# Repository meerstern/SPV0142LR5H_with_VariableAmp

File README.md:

# 可変アンプ内蔵アナログ出力MEMSマイク変換基板 SPV0142LR5H
The Converter board of SPV0142LR5H with Variable Apmlifer

## 概要

  * 最大約50倍の増幅回路[TLV316][0]Syntiant社製[アナログ出力MEMSマイクSPV0142LR5H][1]を搭載した2.54mmピッチ変換基板です。  
  * 可聴音から超音波(100Hz～80kHz)までの幅広い帯域を高感度にセンシングすることが可能です。  
  * 周波数特性が非常にフラットです(20Hz-10kHz±2dB、10kHz-80kHz±10dB)
  * 超音波センサや超音波通信などに使用可能です。  
  * RV1により約1倍～約50倍まで変更することが可能です。  
  * アンプ回路を搭載することでArduinoといったマイコンのアナログ入力に直接接続できます。  
  * マイク穴は基板裏面の丸印部分です。  
  * 電源電圧1.8V~3.6V
  * SPU0410LR5Hの後継品でフットプリントを除いて周波数特性や電気特性がほぼ同じです。

## 超音波マイク比較
 用途に応じて様々な製品をラインアップしています  
| 製品名 | 出力 | アンプ搭載有無 | 用途 | 
|:-----------|:------------|:------------|:------------|
| [アナログ出力マイク][A] | アナログ | 無 | 任意のアンプ回路を使用したい場合 | 
| [可変アンプ内蔵アナログ出力マイク(本製品)][B] | アナログ | 有(可変1~50倍) | 増幅率の調整が必要な場合 |	
| [アンプ内蔵アナログ出力マイク][C] |	アナログ | 有(固定50倍) | 一定した増幅が必要な場合	| 
| [デジタル出力マイク][D] |	デジタルPDM | 不要 | フルデジタルで実装する場合やワイドレンジが必要な場合 | 

## 販売サイト
  * [スイッチサイエンス][2]

## 告知
SPU0410LR5Hの生産完了に伴い、後継品のSPV0142LR5Hに移行しました。

License - MIT

[1]: https://static1.squarespace.com/static/6488b0b8150a045d2d112999/t/67caf41d815fb04909623d2d/1741354016529/SPV0142LR5H-1-datasheet.pdf
[0]: http://www.tij.co.jp/product/jp/TLV316
[2]: https://www.switch-science.com/products/6583

[A]: https://github.com/meerstern/SPV0142LR5H
[B]: https://github.com/meerstern/SPV0142LR5H_with_VariableAmp
[C]: https://github.com/meerstern/SPV0142LR5H_with_Amp
[D]: https://github.com/meerstern/SPH0641LUAmp

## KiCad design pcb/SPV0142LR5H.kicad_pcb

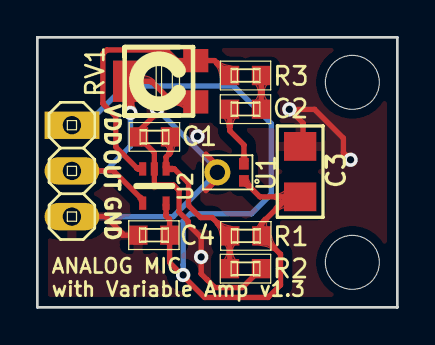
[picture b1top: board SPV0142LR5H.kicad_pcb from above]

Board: 2 copper layers, 20.0 x 15.0 mm, 13 parts (0 on the bottom side), 7 nets.

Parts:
C1, C2: 4.7u; generic-SMD1608
C3: 0.1u; C-1206
C4: 0.1u; generic-SMD1608
P1: Conn_01x03; pinhead-1X03
R1, R2, R3: 10k; generic-SMD1608
REF1, REF2: MountingHole_3mm
RV1: 500k; rcl-RTRIMCVR42A
U1: SPV0142LR5H
U2: LM321; SC-70-5

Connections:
GND: C1.2, C3.2, C4.2, P1.3, R2.1, U1.3, U2.2
MOUT: C2.2, U1.2
unnamed: C1.1, R1.1, R2.2, U2.1
unnamed: C2.1, R3.2
unnamed: R3.1, RV1.3, U2.3
SOUT: P1.2, RV1.1, RV1.2, U2.4
VDD: C3.1, C4.1, P1.1, R1.2, U1.1, U2.5

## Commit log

2026-04-28 Add pcb files
2026-04-28 Add images
